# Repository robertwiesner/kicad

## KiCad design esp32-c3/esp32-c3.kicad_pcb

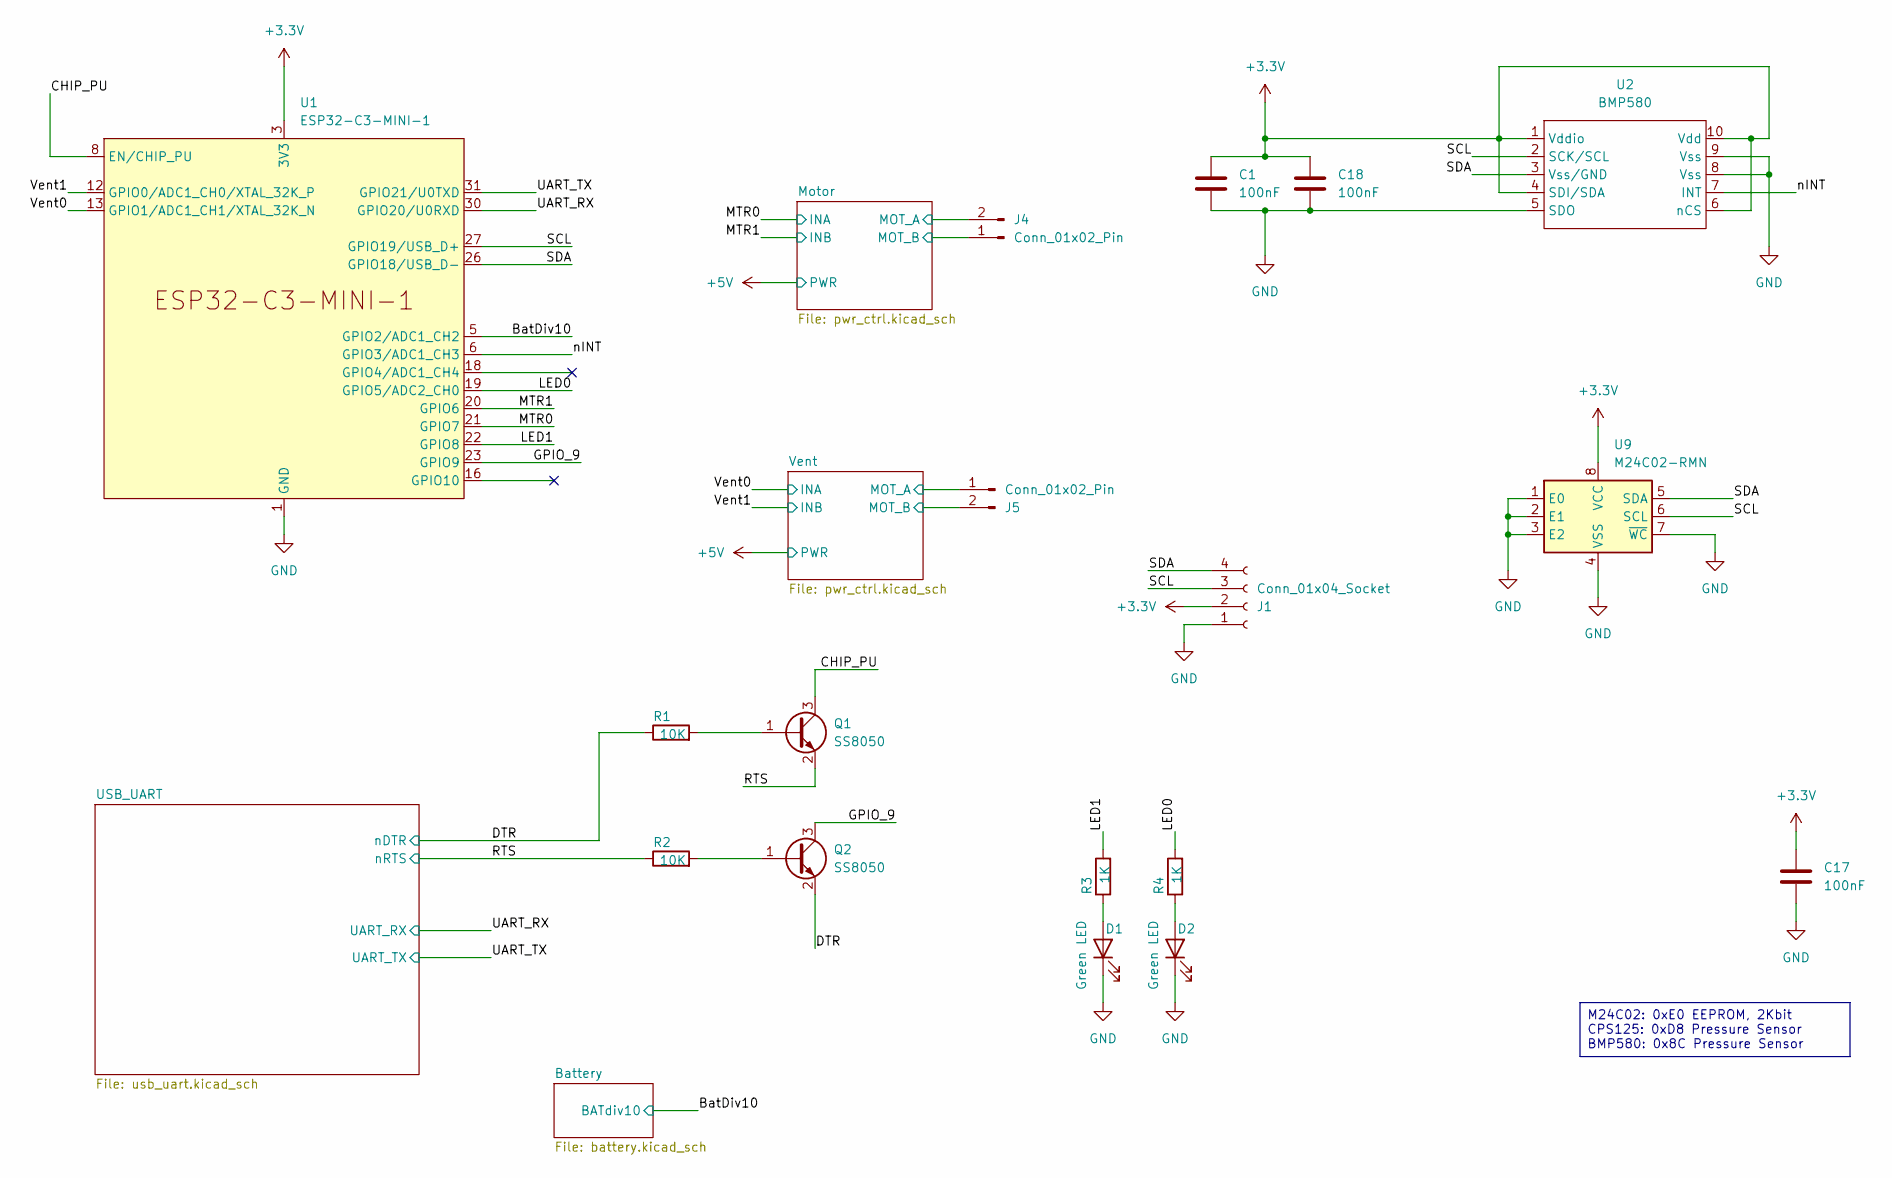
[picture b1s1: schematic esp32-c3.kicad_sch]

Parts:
C1, C17, C18: 100nF; C_0402_1005Metric; LCSC C1525
D1, D2: Green LED; LED_0402_1005Metric; LCSC C434446
J1: Conn_01x04_Socket; PinSocket_1x04_P2.54mm_Vertical
J4, J5: Conn_01x02_Pin; JST_XH_S2B-XH-A-1_1x02_P2.50mm_Horizontal
Q1, Q2: SS8050; SOT-23
R1, R2: 10K; R_0402_1005Metric
R3, R4: 1K; R_0402_1005Metric
U1: ESP32-C3-MINI-1; LCSC C2934569
U2: BMP580; BMP580_FP; LCSC C22391138
U9: M24C02-RMN; SOIC-8_3.9x4.9mm_P1.27mm; LCSC C83836

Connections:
+3.3V: C1.1, C17.1, C18.1, J1.2, U1.3 (3V3), U2.1 (Vddio), U2.4 (SDI/SDA), U2.6 (nCS), U2.10 (Vdd), U9.8 (VCC); also elsewhere on the board
/BatDiv10: U1.5 (GPIO2/ADC1_CH2); also elsewhere on the board
/CHIP_PU: Q1.3 (C), U1.8 (EN/CHIP_PU)
/DTR: Q2.2 (E), R1.1; also elsewhere on the board
/GPIO_9: Q2.3 (C), U1.23 (GPIO9)
/LED0: R4.2, U1.19 (GPIO5/ADC2_CH0)
/LED1: R3.2, U1.22 (GPIO8)
/MTR0: U1.21 (GPIO7); also elsewhere on the board
/MTR1: U1.20 (GPIO6); also elsewhere on the board
/Motor/Mot_a: J4.2; also elsewhere on the board
/Motor/Mot_b: J4.1; also elsewhere on the board
/RTS: Q1.2 (E), R2.1; also elsewhere on the board
/SCL: J1.3, U1.27 (GPIO19/USB_D+), U2.2 (SCK/SCL), U9.6 (SCL)
/SDA: J1.4, U1.26 (GPIO18/USB_D-), U2.3 (Vss/GND), U9.5 (SDA)
/UART_RX: U1.30 (GPIO20/U0RXD); also elsewhere on the board
/UART_TX: U1.31 (GPIO21/U0TXD); also elsewhere on the board
/Vent0: U1.13 (GPIO1/ADC1_CH1/XTAL_32K_N); also elsewhere on the board
/Vent1: U1.12 (GPIO0/ADC1_CH0/XTAL_32K_P); also elsewhere on the board
/Vent/Mot_a: J5.1; also elsewhere on the board
/Vent/Mot_b: J5.2; also elsewhere on the board
/nINT: U1.6 (GPIO3/ADC1_CH3), U2.7 (INT)
GND: C1.2, C17.2, C18.2, D1.1 (K), D2.1 (K), J1.1, U1.1 (GND), U1.2 (GND), U1.11 (GND), U1.14 (GND), U1.36 (GND), U1.37 (GND), U1.38 (GND), U1.39 (GND), U1.40 (GND), U1.41 (GND), U1.42 (GND), U1.43 (GND), U1.44 (GND), U1.45 (GND), U1.46 (GND), U1.47 (GND), U1.48 (GND), U1.49 (GND), U1.50 (GND), U1.51 (GND), U1.52 (GND), U1.53 (GND), U2.5 (SDO), U2.8 (Vss), U2.9 (Vss), U9.1 (E0), U9.2 (E1), U9.3 (E2), U9.4 (VSS), U9.7 (~WC); also elsewhere on the board
unnamed: D1.2 (A), R3.1
unnamed: D2.2 (A), R4.1
unnamed: Q1.1 (B), R1.2
unnamed: Q2.1 (B), R2.2

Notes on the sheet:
M24C02: 0xE0 EEPROM, 2Kbit CPS125: 0xD8 Pressure Sensor BMP580: 0x8C Pressure Sensor

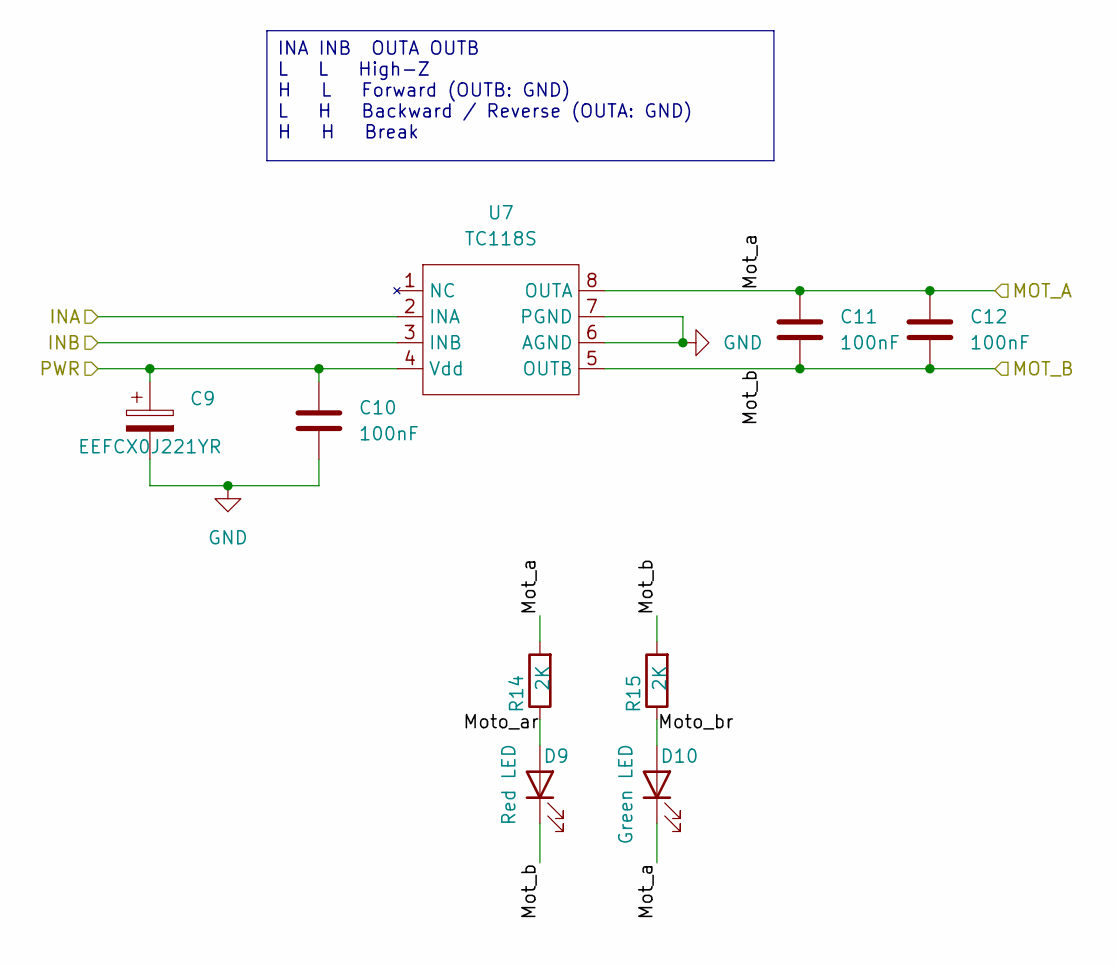
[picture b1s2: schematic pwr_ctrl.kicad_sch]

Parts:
C9: EEFCX0J221YR; CP_SMD_4.3x7.3mm; LCSC C1414444
C10, C11, C12: 100nF; C_0402_1005Metric; LCSC C1525
D9: Red LED; LED_0402_1005Metric; LCSC C264407
D10: Green LED; LED_0402_1005Metric; LCSC C434446
R14, R15: 2K; R_0402_1005Metric
U7: TC118S; SOP-8_3.9x4.9mm_P1.27mm; LCSC C88308

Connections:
+5V: C9.1, C10.1, U7.4 (Vdd); also elsewhere on the board
/MTR0: U7.2 (INA); also elsewhere on the board
/MTR1: U7.3 (INB); also elsewhere on the board
/Motor/Mot_a: C11.1, C12.1, D10.1 (K), R14.2, U7.8 (OUTA); also elsewhere on the board
/Motor/Mot_b: C11.2, C12.2, D9.1 (K), R15.2, U7.5 (OUTB); also elsewhere on the board
/Motor/Moto_ar: D9.2 (A), R14.1
/Motor/Moto_br: D10.2 (A), R15.1
GND: C9.2, C10.2, U7.6 (AGND), U7.7 (PGND); also elsewhere on the board

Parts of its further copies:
C13: EEFCX0J221YR; CP_SMD_4.3x7.3mm; LCSC C1414444
C14, C15, C16: 100nF; C_0402_1005Metric; LCSC C1525
D11: Red LED; LED_0402_1005Metric; LCSC C264407
D12: Green LED; LED_0402_1005Metric; LCSC C434446
R16, R17: 2K; R_0402_1005Metric
U8: TC118S; SOP-8_3.9x4.9mm_P1.27mm; LCSC C88308

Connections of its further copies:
+5V: C13.1, C14.1, U8.4 (Vdd); also elsewhere on the board
/Vent0: U8.2 (INA); also elsewhere on the board
/Vent1: U8.3 (INB); also elsewhere on the board
/Vent/Mot_a: C15.1, C16.1, D12.1 (K), R16.2, U8.8 (OUTA); also elsewhere on the board
/Vent/Mot_b: C15.2, C16.2, D11.1 (K), R17.2, U8.5 (OUTB); also elsewhere on the board
/Vent/Moto_ar: D11.2 (A), R16.1
/Vent/Moto_br: D12.2 (A), R17.1
GND: C13.2, C14.2, U8.6 (AGND), U8.7 (PGND); also elsewhere on the board

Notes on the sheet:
INA INB OUTA OUTB L L High-Z H L Forward (OUTB: GND) L H Backward / Reverse (OUTA: GND) H H Break

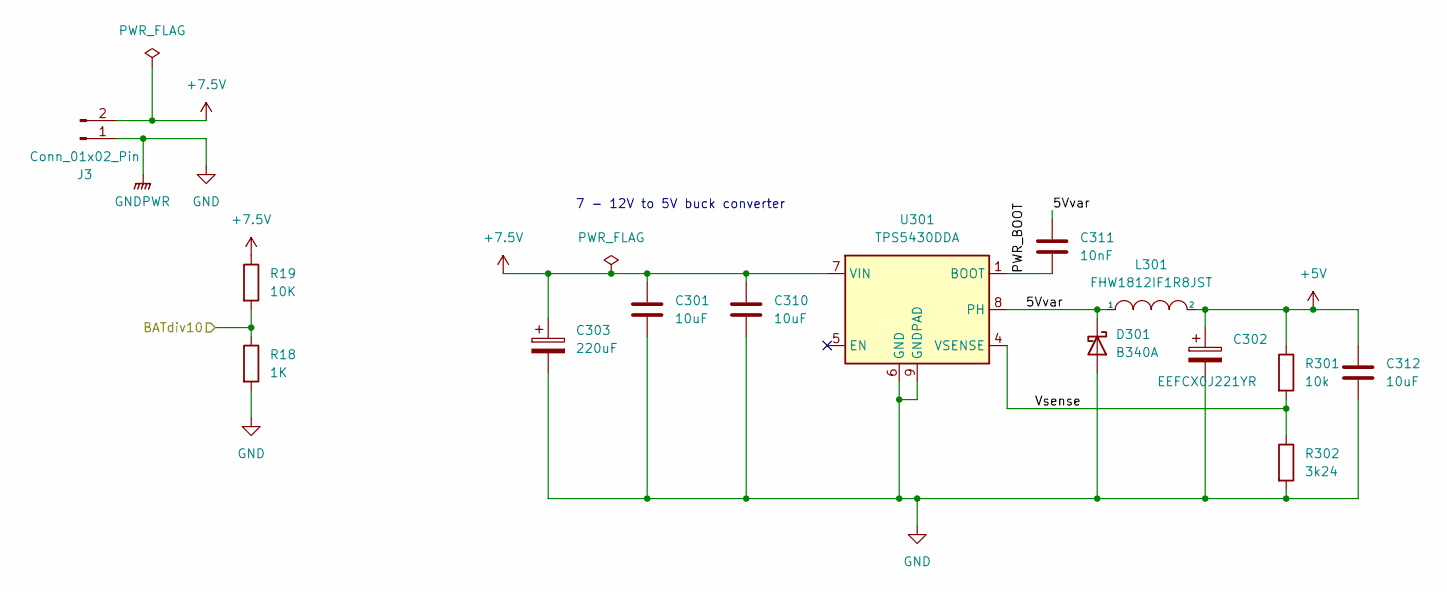
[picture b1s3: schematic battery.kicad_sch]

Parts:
C301, C310, C312: 10uF; C_1206_3216Metric; LCSC C128855
C302: EEFCX0J221YR; CP_SMD_4.3x7.3mm; LCSC C141444
C303: 220uF; CP_EIA-7343-31_Kemet-D; LCSC C8024
C311: 10nF; C_0402_1005Metric; LCSC C2840480
D301: B340A; D_SMA; LCSC C3018525
J3: Conn_01x02_Pin; AMASS_XT30PW-M_1x02_P2.50mm_Horizontal
L301: FHW1812IF1R8JST; L_1812_4532Metric; LCSC C394113
R18: 1K; R_0402_1005Metric
R19: 10K; R_0402_1005Metric
R301: 10k; R_0402_1005Metric; LCSC C60490
R302: 3k24; R_0402_1005Metric; LCSC C327346
U301: TPS5430DDA; TI_SO-PowerPAD-8_ThermalVias; LCSC C9864

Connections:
+5V: C302.1, C312.1, L301.2, R301.1; also elsewhere on the board
+7.5V: C301.1, C303.1, C310.1, J3.2, R19.1, U301.7 (VIN)
/BatDiv10: R18.1, R19.2; also elsewhere on the board
/Battery/5Vvar: C311.2, D301.1 (K), L301.1, U301.8 (PH)
/Battery/PWR_BOOT: C311.1, U301.1 (BOOT)
/Battery/Vsense: R301.2, R302.1, U301.4 (VSENSE)
GND: C301.2, C302.2, C303.2, C310.2, C312.2, D301.2 (A), J3.1, R18.2, R302.2, U301.6 (GND), U301.9 (GNDPAD); also elsewhere on the board

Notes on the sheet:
7 - 12V to 5V buck converter

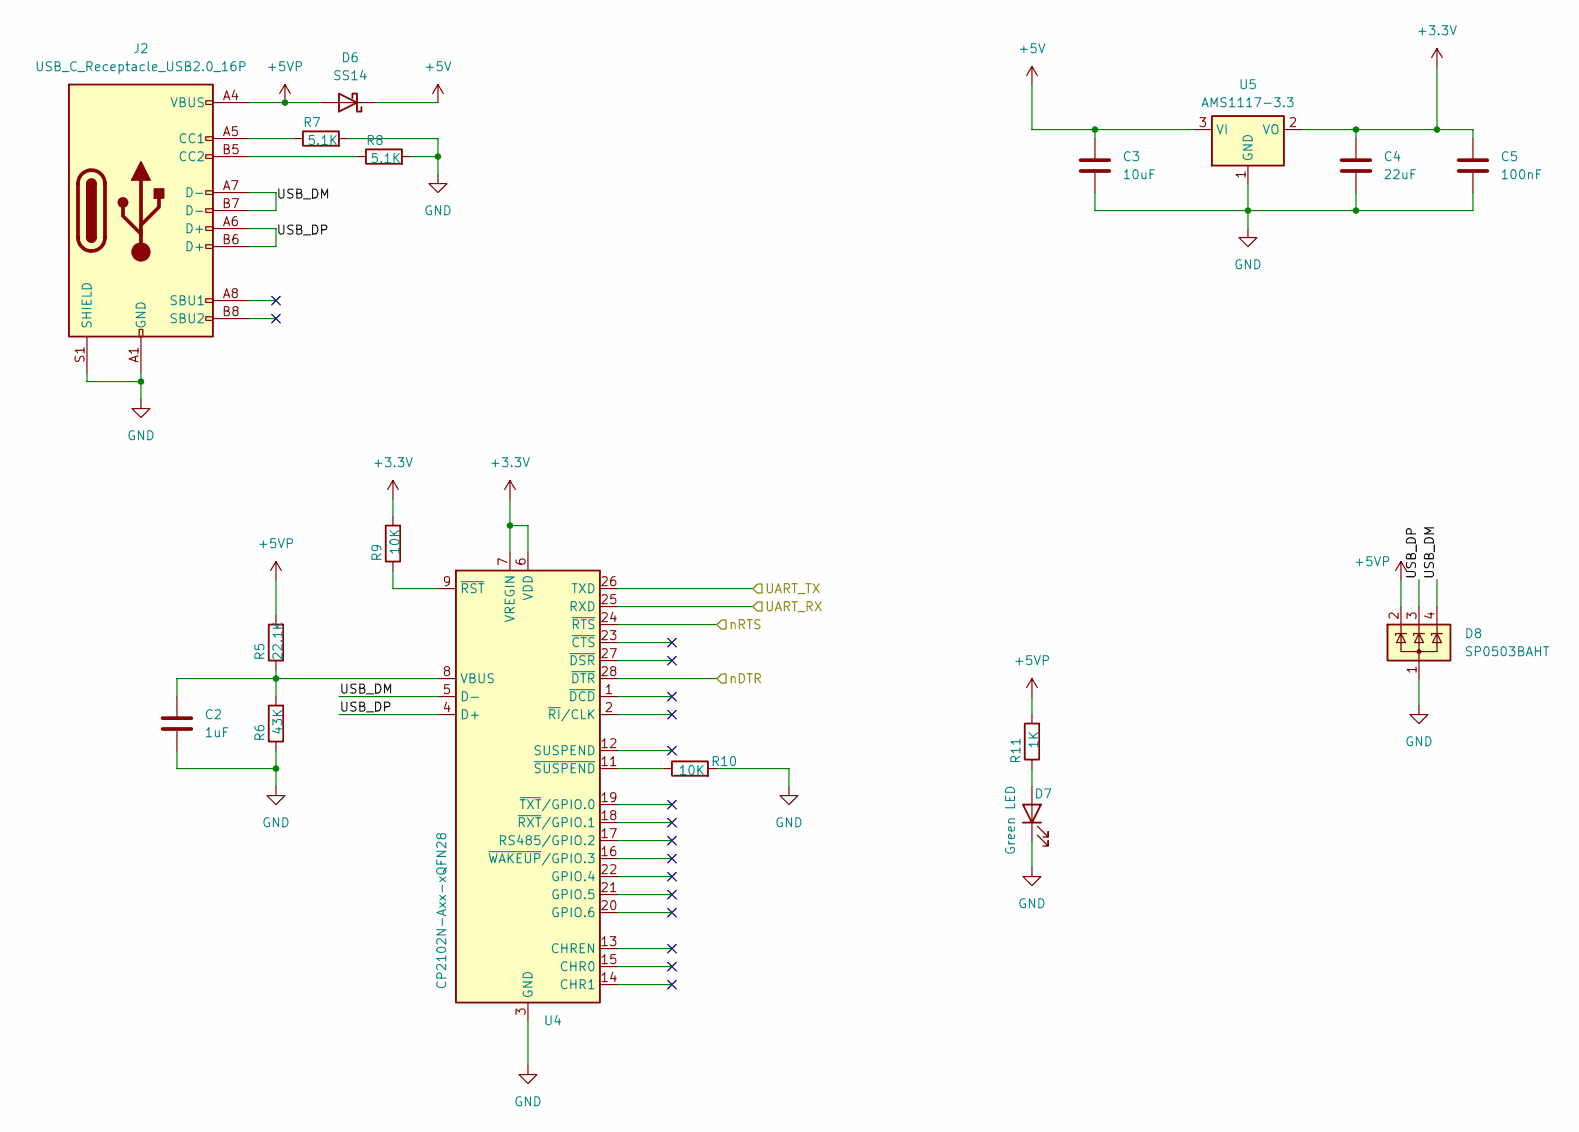
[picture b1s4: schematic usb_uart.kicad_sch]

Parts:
C2: 1uF; C_0402_1005Metric; LCSC C52923
C3: 10uF; C_0805_2012Metric; LCSC C15850
C4: 22uF; C_0805_2012Metric; LCSC C45783
C5: 100nF; C_0402_1005Metric; LCSC C1525
D6: SS14; D_SMA
D7: Green LED; LED_0402_1005Metric; LCSC C434446
D8: SP0503BAHT; SOT-143; LCSC C3040626
J2: USB_C_Receptacle_USB2.0_16P; USB_C_Receptacle_HCTL_HC-TYPE-C-16P-01A; LCSC C2894897
R5: 22.1K; R_0402_1005Metric
R6: 43K; R_0402_1005Metric
R7, R8: 5.1K; R_0402_1005Metric
R9, R10: 10K; R_0402_1005Metric
R11: 1K; R_0402_1005Metric
U4: CP2102N-Axx-xQFN28; QFN-28-1EP_5x5mm_P0.5mm_EP3.35x3.35mm; LCSC C964632
U5: AMS1117-3.3; SOT-223

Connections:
+3.3V: C4.1, C5.1, R9.2, U4.6 (VDD), U4.7 (VREGIN), U5.2 (VO); also elsewhere on the board
+5V: C3.1, D6.1 (K), U5.3 (VI); also elsewhere on the board
+5VP: D6.2 (A), D8.2 (K), J2.A4 (VBUS), J2.A9 (VBUS), J2.B4 (VBUS), J2.B9 (VBUS), R5.2, R11.2
/DTR: U4.28 (~DTR); also elsewhere on the board
/RTS: U4.24 (~RTS); also elsewhere on the board
/UART_RX: U4.25 (RXD); also elsewhere on the board
/UART_TX: U4.26 (TXD); also elsewhere on the board
/USB_UART/USB_DM: D8.4 (K), J2.A7 (D-), J2.B7 (D-), U4.5 (D-)
/USB_UART/USB_DP: D8.3 (K), J2.A6 (D+), J2.B6 (D+), U4.4 (D+)
GND: C2.2, C3.2, C4.2, C5.2, D7.1 (K), D8.1 (A), J2.A1 (GND), J2.A12 (GND), J2.B1 (GND), J2.B12 (GND), J2.S1 (SHIELD), R6.1, R7.2, R8.2, R10.2, U4.3 (GND), U4.29 (GND), U5.1 (GND); also elsewhere on the board
unnamed: D7.2 (A), R11.1
unnamed: J2.A5 (CC1), R7.1
unnamed: J2.B5 (CC2), R8.1
unnamed: C2.1, R5.1, R6.2, U4.8 (VBUS)
unnamed: R9.1, U4.9 (~RST)
unnamed: R10.1, U4.11 (~SUSPEND)

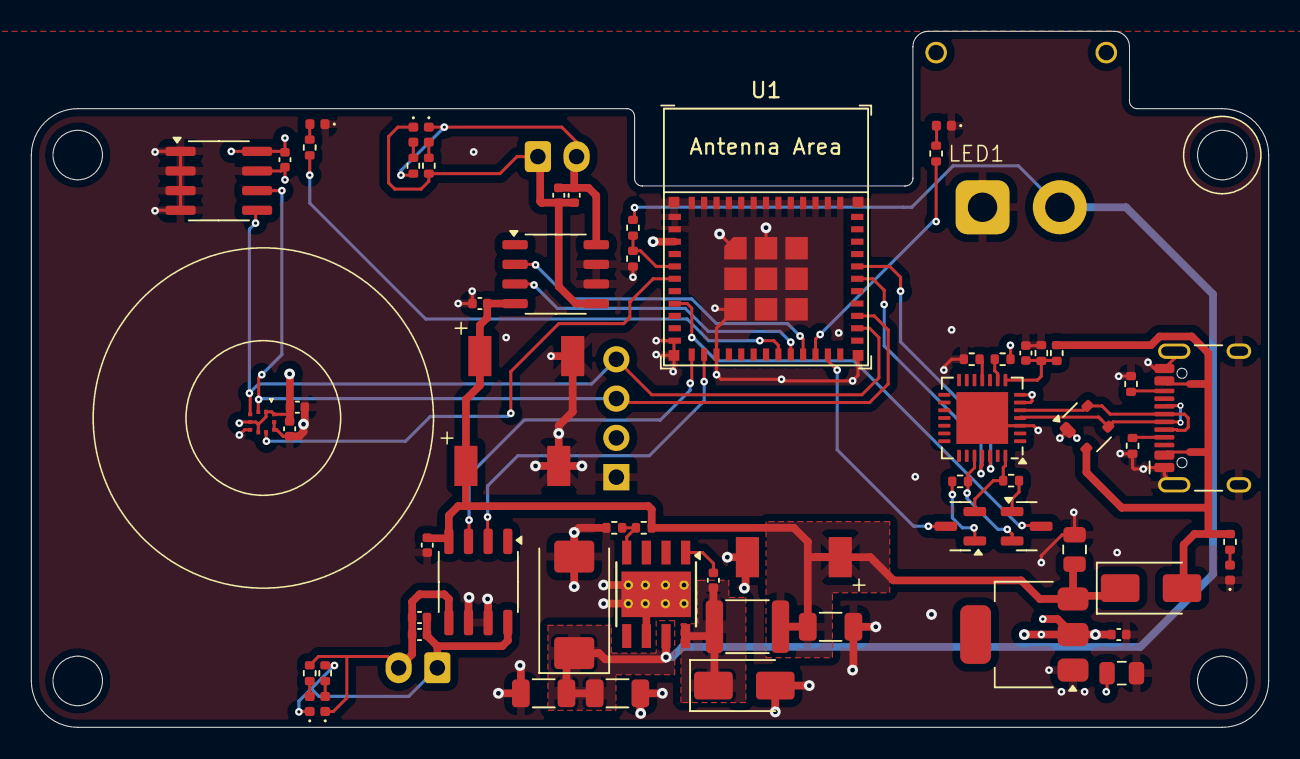
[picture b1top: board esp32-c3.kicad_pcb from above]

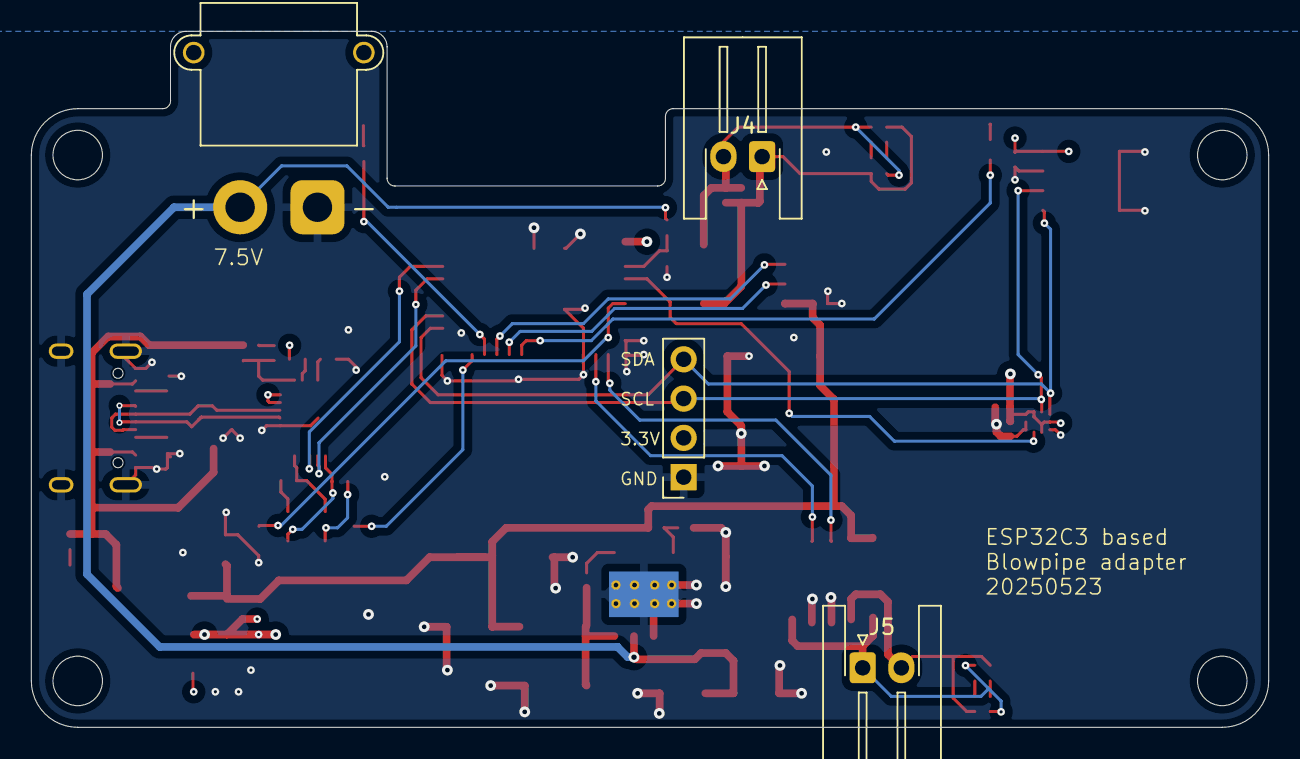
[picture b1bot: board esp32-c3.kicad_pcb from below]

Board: 4 copper layers, 80.0 x 45.0 mm, 66 parts (4 on the bottom side), 44 nets.

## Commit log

2025-04-12 initial checkin
2025-05-24 Fix Battery power and USB/UART connection, move vent around to accomodate enclosure
2025-05-24 add new files
